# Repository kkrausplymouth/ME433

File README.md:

# ME433
MECH_ENG 433 Coursework

Homeworks Range from CAD, to PCB Design, to microcrontroller programming projects. Below is a list of each folder and the project it contains:

Final Project - Line following robot using image processing from a camera, a PIC32 Microcontroller, Raspberry PI, and brushed motors

Fun/Testing - Random assortment of tests to develop my skills

HW10 - LED Strip Contol using PIC32 Microcontroller

HW11 - Performing an FFT using a Raspberry PI Microcontroller

HW10 - Cube CAD Files to be manufactured using 2D Laser Cutting Methods

HW14 - Servo Motor Driver using PIC32 Microcontroller

HW2 - Simple PIC32 Programs that repeats back characters typed to esure proper wiring of cuircuit

HW3 - Plotter Program, to be used in later coursework

HW4 - PCB Design of PIC Breadboarded Circuit to manufacture a PCB Microcontroller Circuit

HW5 - Wave generation using PIC32 Microcontroller

HW6 - IO Extender using i2c Protocol

HW7 - Accelorometer Data Collector using PIC32 and i2c

HW8 - Screen Display w/ Accelorometer

HW9 - Python Signal Filtering

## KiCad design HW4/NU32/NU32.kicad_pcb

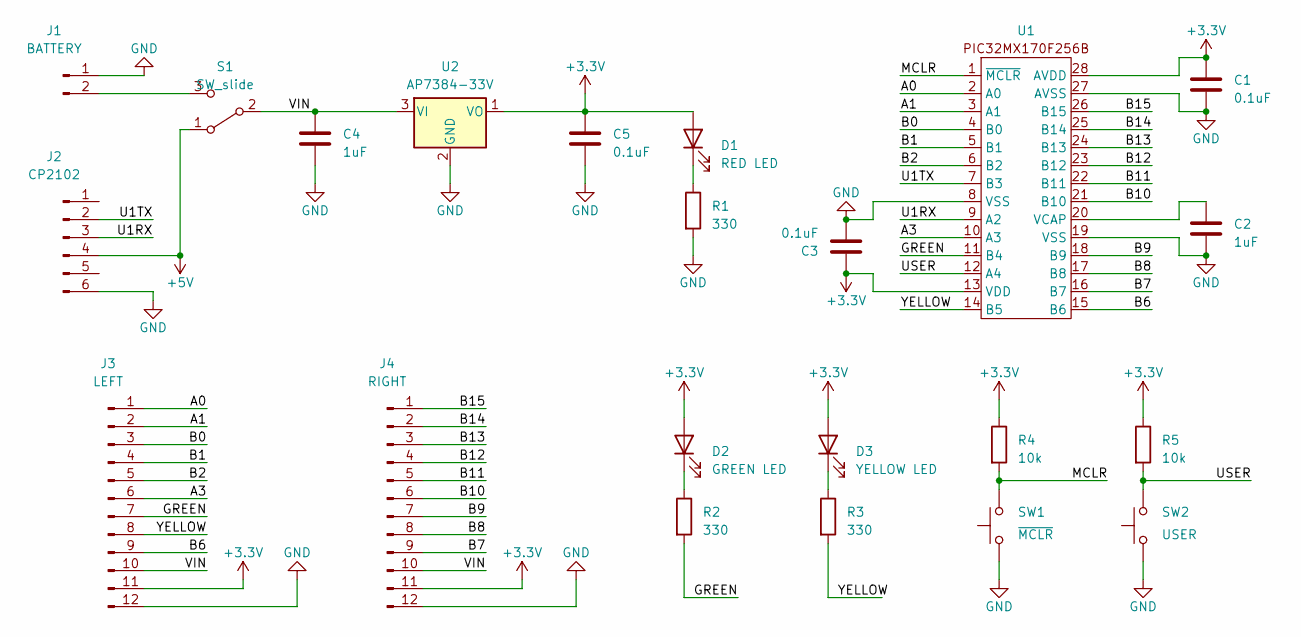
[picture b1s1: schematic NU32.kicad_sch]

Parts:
C1, C3, C5: 0.1uF; C_Disc_D3.4mm_W2.1mm_P2.50mm
C2, C4: 1uF; C_Disc_D4.3mm_W1.9mm_P5.00mm
D1: RED LED; LED_D3.0mm
D2: GREEN LED; LED_D3.0mm
D3: YELLOW LED; LED_D3.0mm
J1: BATTERY; PinSocket_1x02_P2.54mm_Vertical
J2: CP2102; PinSocket_1x06_P2.54mm_Vertical
J3: LEFT; PinSocket_1x12_P2.54mm_Vertical
J4: RIGHT; PinSocket_1x12_P2.54mm_Vertical
R1, R2, R3: 330; R_Axial_DIN0204_L3.6mm_D1.6mm_P7.62mm_Horizontal
R4, R5: 10k; R_Axial_DIN0204_L3.6mm_D1.6mm_P7.62mm_Horizontal
S1: SW_slide; slidesw
SW1: ~{MCLR}; Pushbutton
SW2: USER; Pushbutton
U1: DIP-28_W7.62mm_Socket
U2: AP7384-33V; TO-92L_Inline

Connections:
+3.3V: C1.1, C3.1, C5.1, D1.2 (A), D2.2 (A), D3.2 (A), J3.11, J4.11, R4.1, R5.1, U1.13 (VDD), U1.28 (AVDD), U2.1 (VO)
+5V: J2.4, S1.1 (A)
/A0: J3.1, U1.2 (A0)
/A1: J3.2, U1.3 (A1)
/A3: J3.6, U1.10 (A3)
/B0: J3.3, U1.4 (B0)
/B1: J3.4, U1.5 (B1)
/B2: J3.5, U1.6 (B2)
/B6: J3.9, U1.15 (B6)
/B7: J4.9, U1.16 (B7)
/B8: J4.8, U1.17 (B8)
/B9: J4.7, U1.18 (B9)
/B10: J4.6, U1.21 (B10)
/B11: J4.5, U1.22 (B11)
/B12: J4.4, U1.23 (B12)
/B13: J4.3, U1.24 (B13)
/B14: J4.2, U1.25 (B14)
/B15: J4.1, U1.26 (B15)
/GREEN: J3.7, R2.2, U1.11 (B4)
/MCLR: R4.2, SW1.2, U1.1 (~MCLR)
/U1RX: J2.3, U1.9 (A2)
/U1TX: J2.2, U1.7 (B3)
/USER: R5.2, SW2.2, U1.12 (A4)
/VIN: C4.1, J3.10, J4.10, S1.2 (B), U2.3 (VI)
/YELLOW: J3.8, R3.2, U1.14 (B5)
GND: C1.2, C2.2, C3.2, C4.2, C5.2, J1.1, J2.6, J3.12, J4.12, R1.2, SW1.1, SW2.1, U1.8 (VSS), U1.19 (VSS), U1.27 (AVSS), U2.2 (GND)
unnamed: D1.1 (K), R1.1
unnamed: D2.1 (K), R2.1
unnamed: D3.1 (K), R3.1
unnamed: J1.2, S1.3 (C)
unnamed: C2.1, U1.20 (VCAP)

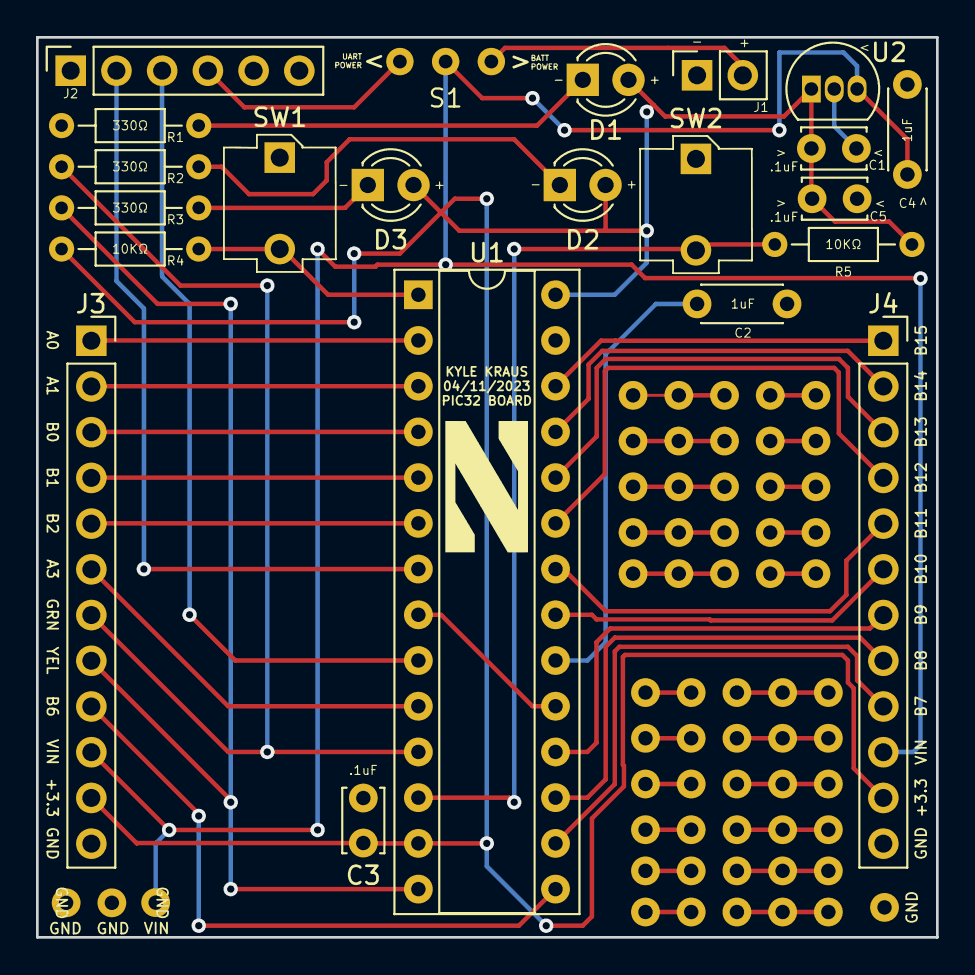
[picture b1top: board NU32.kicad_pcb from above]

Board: 2 copper layers, 50.0 x 50.0 mm, 22 parts (0 on the bottom side), 31 nets.

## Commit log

2023-04-03 Homework 2
    PIC Setup and Blinking LED Program
2023-04-05 HW3
    Added the code for a sine wave generator
2023-04-14 HW4
    Kicad files for PIC32 Board
2023-04-20 HW5
    SPI Waves (WHY ARE THEY SPIKEY!? ahhhhhhhhhh!)
2023-04-22 HW 6 + 7
    i2c I/O expander and accelerometer
2023-04-25 HW 8
    Accelerometer with Display
2023-05-03 HW9
    Data Processing and Filtering
2023-05-04 HW10
    RGB LED Control
2023-05-16 HW11
    PicoW Stuff
2023-05-17 HW12
    Panel CAD
2023-05-18 HW12 Update
    Added Wheel File
2023-05-24 HW14
    Servo Motor Control
2023-06-08 HW15 + Final Project
    Cameral Line Detection and Line following Robot Creation
